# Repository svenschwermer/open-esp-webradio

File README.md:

# Open ESP Webradio
This project aims to build a webradio based on the ESP8266. The goal is to make
it controllable via touchscreen.

_This respository and the entire project is very much work-in-progress…_

## Hardware
The incoming encoded audio stream is buffered in an external SPI RAM. The ESP8266
has two hardware SPI controllers: SPI0 (aka SPI) and SPI1 (aka HSPI). The ESP-12F
module that is used here uses SPI0 for accessing the SPI flash memory that holds
the program data. Here, HSPI is used for accessing the SPI RAM. Since the pins
that are regularly used for HSPI will be used for talking I2S to the audio DAC,
SPI0 and HSPI are configured in overlap mode. That means, that they share the same
pins (except for the CS line). There is an arbiter that selects which SPI controller
gets to access the pins. The SPI RAM device here is a 23LC1024 which has a capacity
of 1 Mbit. Both the ESP8266 and the 23LC1024 support Quad SPI where all data lines
(SIO0..3) are bidirectional, so 4 bits are transferred in every clock cycle.

The audio DAC that is used here is the WM8731. The audio data is transferred using
I2S via the I2S controller that is built into the ESP8266. The configuration of
the DAC is performed via I2C. Even though the ESP8266 contains an I2C controller,
it is not used here, because the pins were not available. Since the WM8731 comes
with a microphone interface, it is included together with the reverse I2S direction.

The display that is used here, is a MI0283QT 240x320 color LCD. Infos about the
adapter board that molds a touchscreen controller as well, can be found
[here](https://github.com/watterott/MI0283QT-Adapter). Both the LCD controller and
the touchscreen controller are also sharing the same SPI pins as the SPI flash and
the SPI RAM. Both are controlled by the HSPI controller. The LCD uses a hardware
CS, but for the touchscreen controller, there was no more hardware CS available
that is not used for anything else. Hence, GPIO16 is used as the CS line for the
touchscreen controller.

### Schematic

#### Remarks
- The SPI RAM is wired incorrectly: SIO2 and SIO3 should be swapped. This is
  fixed in software.

## Software
To build the software, follow the instructions in the
[open-esp-webradio repository](https://github.com/SuperHouse/esp-open-rtos) to
install the required toolchain. Then simply run `make` or `make flash`,
respectively, to compile or flash the image. The WiFi credentials should be
supplied via the file `./esp-open-rtos/include/private_ssid_config.h`.

## Credits
Inspired by [ESP8266_MP3_DECODER](https://github.com/espressif/ESP8266_MP3_DECODER),
this project builds upon the following components:
- [open-esp-webradio](https://github.com/SuperHouse/esp-open-rtos)
- [libmad](https://www.underbit.com/products/mad)

## License
This project is licensed under the terms of the GNU GPLv3, see [LICENSE.md](LICENSE.md).

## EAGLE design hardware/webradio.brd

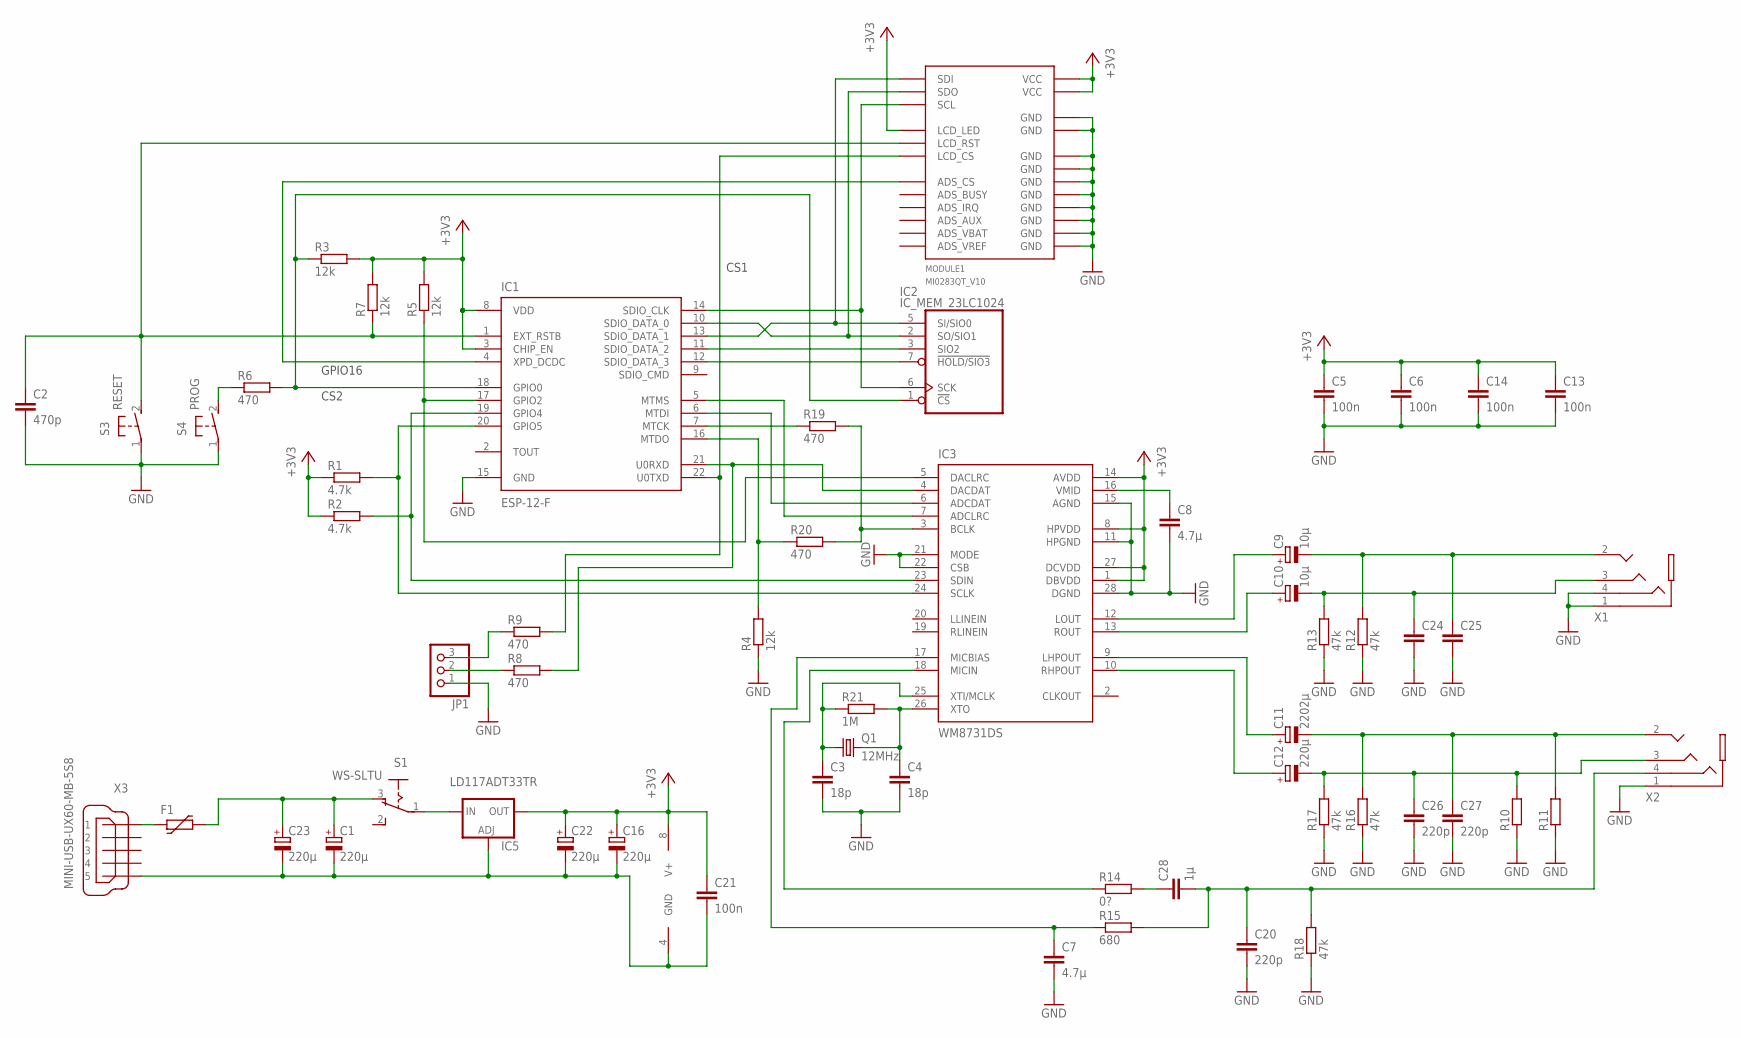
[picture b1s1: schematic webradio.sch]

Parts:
C1, C16, C22, C23: 220µ; B/3528-21R
C2: 470p; C0805
C3, C4: 18p; C0805
C5, C6, C13, C14, C21: 100n; C0805
C7, C8: 4.7µ; C0805
C9, C10: 10µ; A/3216-18R
C11: 2202µ; D/7343-31R
C12: 220µ; D/7343-31R
C20, C26, C27: 220p; C0805
C24, C25: C-EUC0805; C0805
C28: 1µ; C0805
F1: FUSE_PTC-1812; PTC1812L
IC1: ESP-12-F
IC2: IC_MEM_23LC1024; SOIC-8
IC3: WM8731DS; SSOP28
IC5: LD117ADT33TR; DPACK
JP1: PINHD-1X3/90; 1X03/90
MODULE1: MI0283QT_V10
Q1: 12MHz; HC49UP
R1, R2: 4.7k; R0805
R3, R4, R5, R7: 12k; R0805
R6, R8, R9, R19, R20: 470; R0805
R10, R11: R-EU_R0805; R0805
R12, R13, R16, R17, R18: 47k; R0805
R14: 0?; R0805
R15: 680; R0805
R21: 1M; R0805
S1: WS-SLTU; 450302014072
S3: RESET; B3F-31XX
S4: PROG; B3F-31XX
X1, X2: SJ-43514-SMT
X3: MINI-USB-UX60-MB-5S8; UX60-MB-5S8

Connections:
+3V3: C5.1, C6.1, C13.1, C14.1, C16.+, C21.1, C22.+, IC1.3 (CHIP_EN), IC1.8 (VDD), IC2.8 (V+), IC3.1 (DBVDD), IC3.8 (HPVDD), IC3.14 (AVDD), IC3.27 (DCVDD), IC5.4 (OUT), MODULE1.3_VCC (VCC), MODULE1.4_VCC (VCC), MODULE1.5_LCD_LED (LCD_LED), R1.1, R2.1, R3.2, R5.2, R7.2
GND: C1.-, C2.2, C3.2, C4.2, C5.2, C6.2, C7.2, C8.2, C13.2, C14.2, C16.-, C20.2, C21.2, C22.-, C23.-, C24.2, C25.2, C26.2, C27.2, IC1.15 (GND), IC2.4 (GND), IC3.11 (HPGND), IC3.15 (AGND), IC3.21 (MODE), IC3.22 (CSB), IC3.28 (DGND), IC5.1 (ADJ), JP1.1, MODULE1.1_GND (GND), MODULE1.2_GND (GND), MODULE1.GND_1 (GND), MODULE1.GND_2 (GND), MODULE1.GND_3 (GND), MODULE1.GND_4 (GND), MODULE1.GND_5 (GND), MODULE1.GND_6 (GND), MODULE1.GND_7 (GND), MODULE1.GND_8 (GND), R4.1, R10.1, R11.1, R12.1, R13.1, R16.1, R17.1, R18.1, S3.1, S4.1, X1.1, X1.4, X2.1, X3.5
unnamed: IC1.14 (SDIO_CLK), IC2.6 (SCK), MODULE1.10_SCL (SCL)
unnamed: IC1.18 (GPIO0), IC2.1 (!CS), R3.1, R6.2
unnamed: F1.1, X3.1
unnamed: IC1.10 (SDIO_DATA_0), IC2.2 (SO/SIO1), MODULE1.9_SDO (SDO)
unnamed: IC1.11 (SDIO_DATA_2), IC2.3 (SIO2)
unnamed: IC1.12 (SDIO_DATA_3), IC2.7 (!HOLD/SIO3)
unnamed: IC1.16 (MTDO), R4.2, R20.1
unnamed: IC1.21 (U0RXD), IC3.4 (DACDAT), R8.2
unnamed: IC1.17 (GPIO2), IC3.5 (DACLRC), R5.1
unnamed: IC1.19 (GPIO4), IC3.23 (SDIN), R2.2
unnamed: IC1.20 (GPIO5), IC3.24 (SCLK), R1.2
unnamed: R6.1, S4.2 (S)
unnamed: JP1.2, R8.1
unnamed: C2.1, IC1.1 (EXT_RSTB), MODULE1.6_LCD_RST (LCD_RST), R7.1, S3.2 (S)
unnamed: IC1.22 (U0TXD), MODULE1.7_LCD_CS (LCD_CS), R9.2
unnamed: JP1.3, R9.1
unnamed: C3.1, IC3.25 (XTI/MCLK), Q1.1, R21.1
unnamed: C4.1, IC3.26 (XTO), Q1.2, R21.2
unnamed: C1.+, C23.+, F1.2, S1.3 (O)
unnamed: C8.1, IC3.16 (VMID)
unnamed: C10.+, IC3.13 (ROUT)
unnamed: C9.+, IC3.12 (LOUT)
unnamed: C9.-, C25.1, R12.2, X1.2
unnamed: C10.-, C24.1, R13.2, X1.3
unnamed: C12.+, IC3.10 (RHPOUT)
unnamed: C11.+, IC3.9 (LHPOUT)
unnamed: C11.-, C27.1, R11.2, R16.2, X2.2
unnamed: C12.-, C26.1, R10.2, R17.2, X2.3
unnamed: IC5.3 (IN), S1.1
unnamed: C7.1, IC3.17 (MICBIAS), R15.1
unnamed: IC3.18 (MICIN), R14.1
unnamed: C28.1, R14.2
unnamed: C20.1, C28.2, R15.2, R18.2, X2.4
unnamed: IC1.6 (MTDI), IC3.6 (ADCDAT)
unnamed: IC1.5 (MTMS), IC3.7 (ADCLRC)
unnamed: IC1.7 (MTCK), R19.1
unnamed: IC3.3 (BCLK), R19.2, R20.2
unnamed: IC1.13 (SDIO_DATA_1), IC2.5 (SI/SIO0), MODULE1.8_SDI (SDI)
unnamed: IC1.4 (XPD_DCDC), MODULE1.11_ADS_CS (ADS_CS)

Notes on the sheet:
CS1
CS2
GPIO16

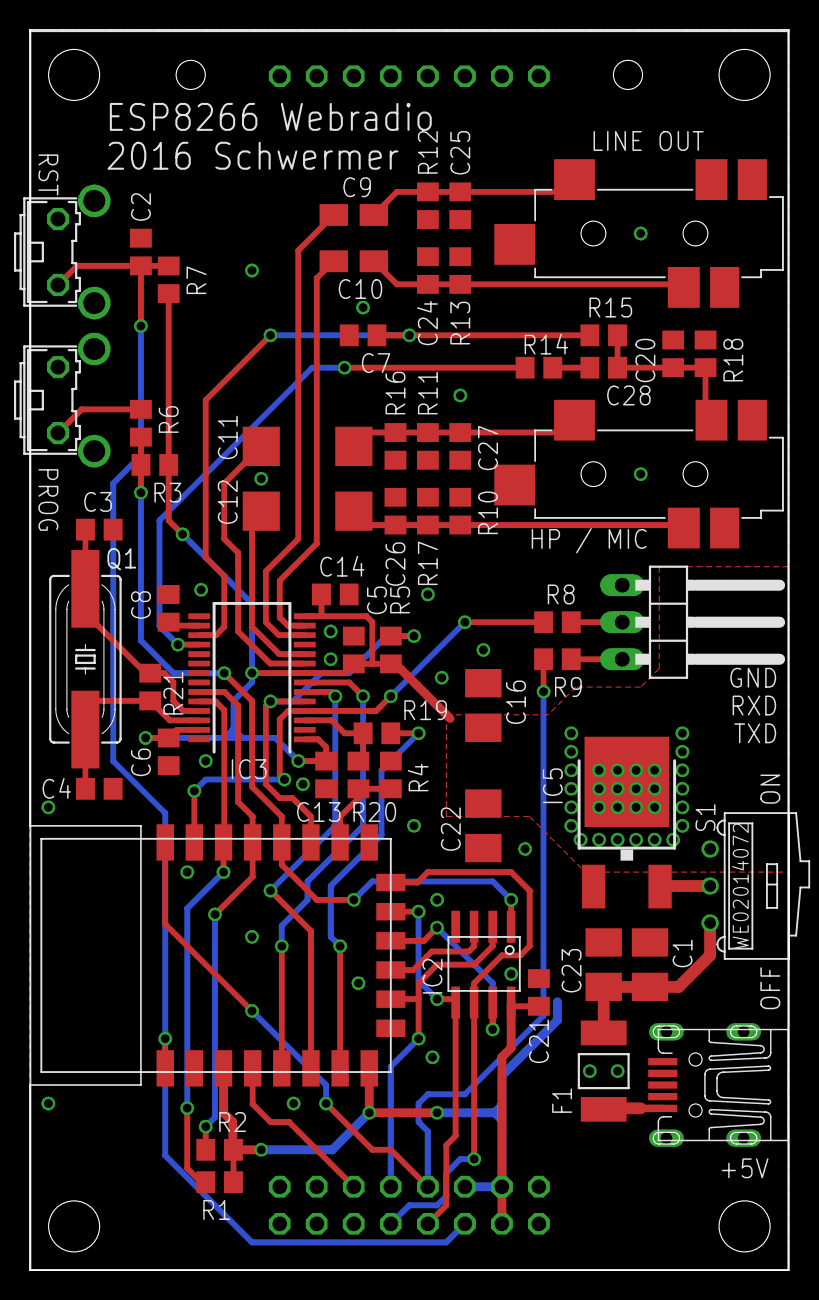
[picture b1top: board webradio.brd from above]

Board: 2 copper layers, 52.1 x 85.1 mm, 59 parts (0 on the bottom side), 41 nets.

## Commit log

2017-11-04 Skeleton for open webradio
2017-11-05 Working SPI RAM based FIFO
2017-11-05 Functional HTTP streaming to FIFO
2017-11-05 First seemingly working version
2017-11-05 I2S code added, but not functional yet
2017-11-11 At least we're getting some noise
2017-11-11 Streaming, decoding & I2S work
    There is still some distortion, though.
2017-11-11 Distortion removed
2017-11-11 Use GitHub URL for libmad submodule
2017-11-19 Enable stereo decoding
2017-11-19 Fine-tune required task stack sizes
2017-11-19 Make libmad allocate buffers statically
2017-11-25 Fix SPIRAM reliability issues
    Force the RAM into sequential mode upon bootup.
2017-11-26 Separate HSPI code from SPIRAM code
2017-11-26 Working state for regular (non-QIO) SPI
2017-11-26 SPIRAM functional in QIO mode
2017-11-26 Complete SPI register definition
2017-11-26 LCD init & fill functional
2017-11-26 Allow different SPI users to use different clocks
2017-11-27 Change to 128 kbit/s 44.1 kHz stream
2017-11-27 Refactor SPI instances
2018-01-14 Reduce buffer size for libmad
2018-01-16 Increase mp3 decoder prio to avoid underruns
2018-01-16 Resolve merge errors
2018-01-16 Update esp-open-rtos
2018-01-17 Add lcd_write_pixels
2018-01-18 Add simple monospace font
2018-01-18 Add simple terminal on LCD
2018-01-19 Rework terminal
    Allow successive printf calls to print to the same line. Remove mutex from terminal code, as it seems to be redundant.
2018-01-19 Fix terminal handling empty lines
2018-01-19 Print periodic status info
2018-01-25 First successful tries to talk to the ADS7846
2018-01-25 Continuous touch controller sampling during playback
2018-01-26 Add readme and schematic
2018-01-26 Add Eagle schematic and board design
2018-01-26 Add license
2018-01-27 Make terminal resizable
2018-01-27 clang-format stream_client.c
2018-01-28 Parsing stream metadata functional
2018-01-28 Metadata extraction working with decoding
2018-01-28 Create common utility header
2018-01-28 Add metadata callback mechanism
2018-01-28 Change sample rate based on mp3 frame
2018-01-28 Make stream stoppable
2018-01-31 First unfinished model
2018-02-25 Final case
2018-02-25 Basis for UI
2018-02-26 Touchscreen buttons functional
2018-02-26 Stream start/stoppable per UI
2018-02-26 Make channel selectable via UI
2018-02-26 Add channels
2018-02-26 Fix deadlock when stopping playback
